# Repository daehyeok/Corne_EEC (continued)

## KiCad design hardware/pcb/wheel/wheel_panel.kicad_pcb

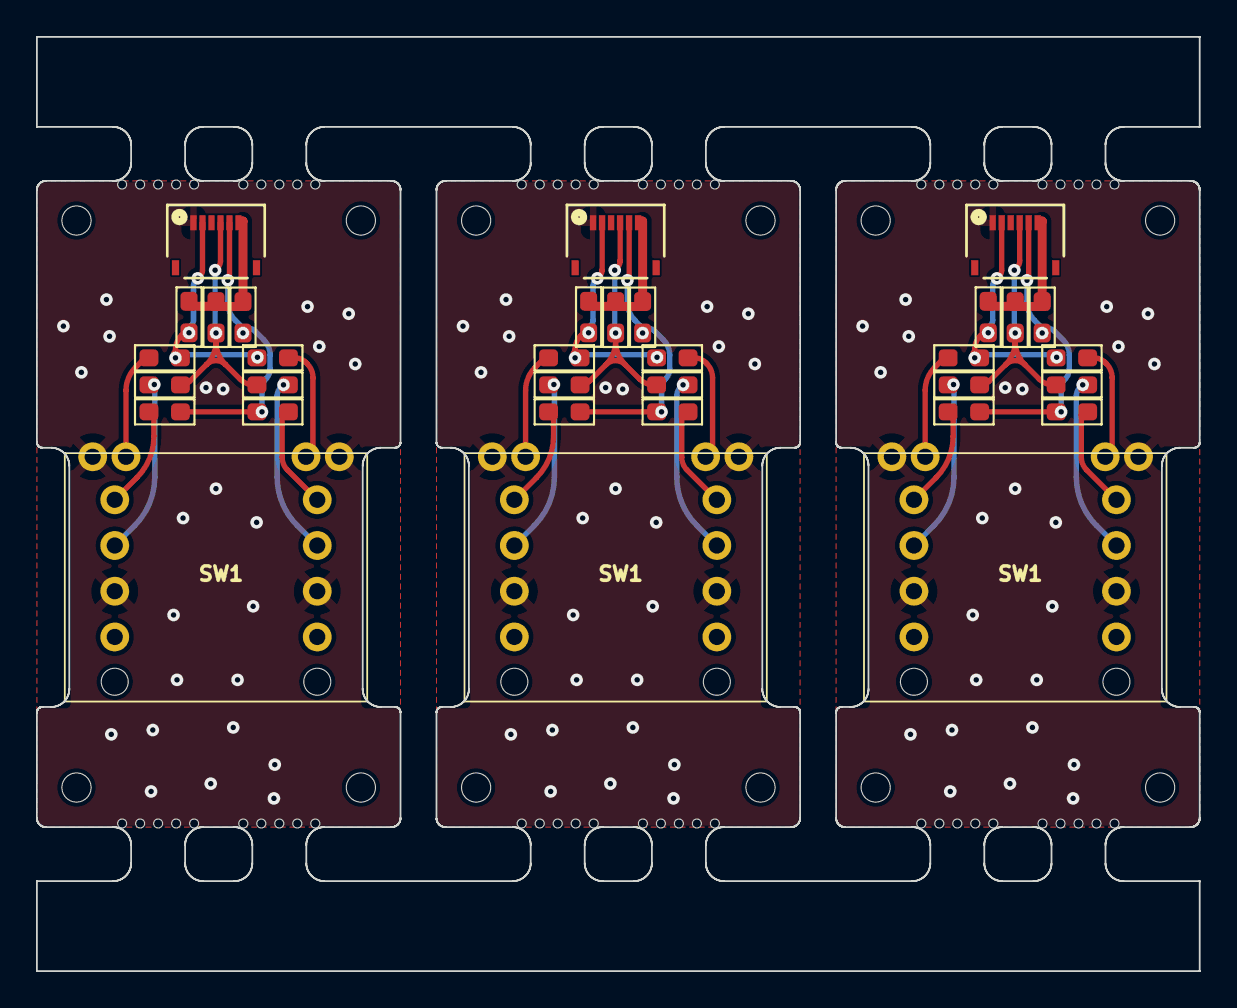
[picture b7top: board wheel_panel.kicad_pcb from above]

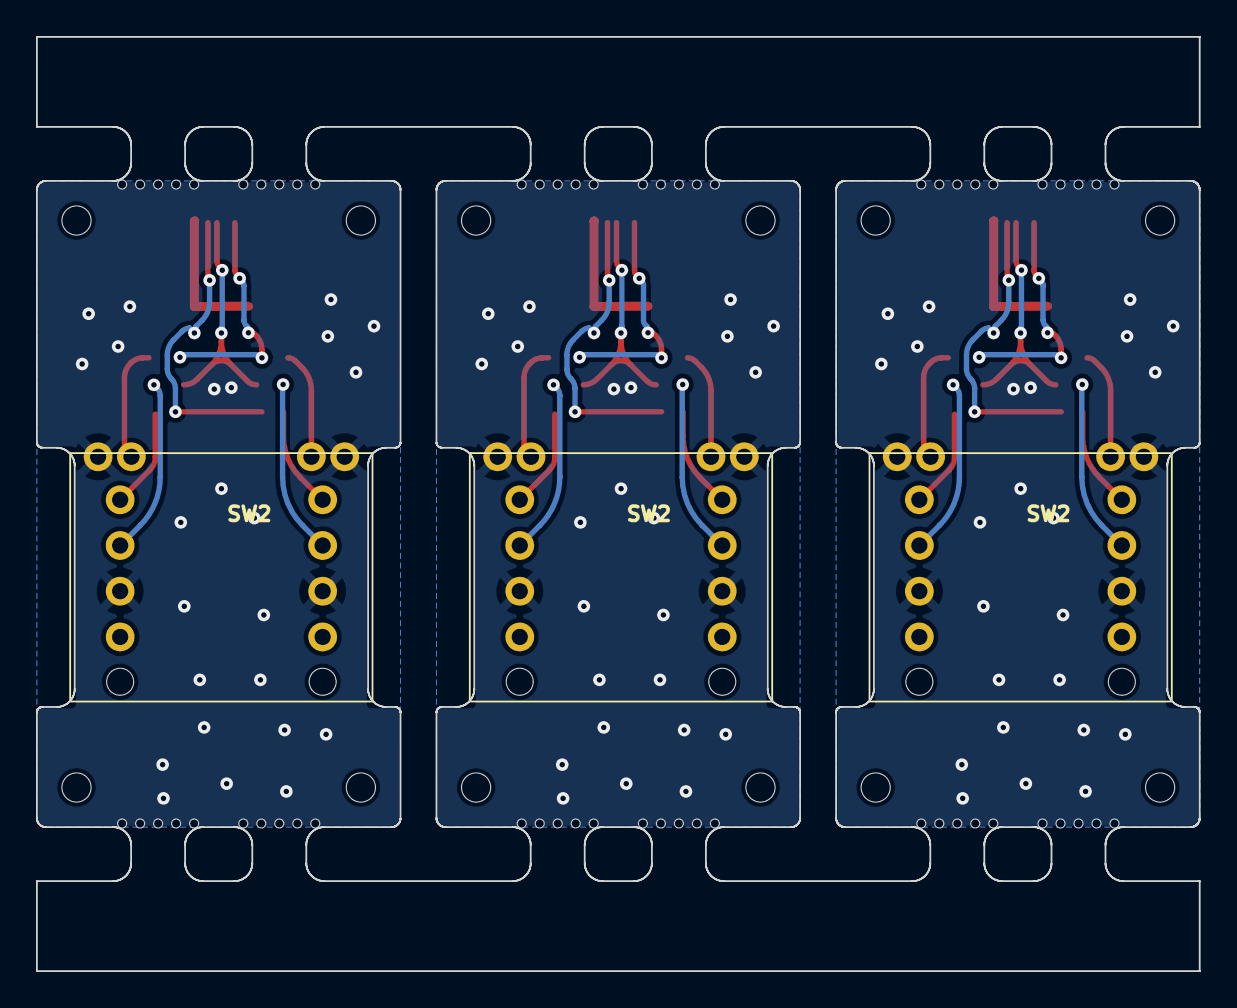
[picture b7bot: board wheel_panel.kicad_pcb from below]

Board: 2 copper layers, 64.6 x 51.9 mm, 108 parts (3 on the bottom side), 33 nets.

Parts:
H3, H3#2, H3#3, H4, H4#2, H4#3, H5, H5#2, H5#3, H6, H6#2, H6#3: SMT-SO-M1.6-with-ring
J4, J4#2, J4#3: HRS_FH34SRJ-06S-0.5SH(50); CONN6x1_FH34SRJ-6S-0.5SH50_HIR
KiKit_MB_1_1, KiKit_MB_1_2, KiKit_MB_1_3, KiKit_MB_1_4, KiKit_MB_1_5, KiKit_MB_2_1, KiKit_MB_2_2, KiKit_MB_2_3, KiKit_MB_2_4, KiKit_MB_2_5, KiKit_MB_3_1, KiKit_MB_3_2, KiKit_MB_3_3, KiKit_MB_3_4, KiKit_MB_3_5, KiKit_MB_4_1, KiKit_MB_4_2, KiKit_MB_4_3, KiKit_MB_4_4, KiKit_MB_4_5, KiKit_MB_5_1, KiKit_MB_5_2, KiKit_MB_5_3, KiKit_MB_5_4, KiKit_MB_5_5, KiKit_MB_6_1, KiKit_MB_6_2, KiKit_MB_6_3, KiKit_MB_6_4, KiKit_MB_6_5, KiKit_MB_7_1, KiKit_MB_7_2, KiKit_MB_7_3, KiKit_MB_7_4, KiKit_MB_7_5, KiKit_MB_8_1, KiKit_MB_8_2, KiKit_MB_8_3, KiKit_MB_8_4, KiKit_MB_8_5, KiKit_MB_9_1, KiKit_MB_9_2, KiKit_MB_9_3, KiKit_MB_9_4, KiKit_MB_9_5, KiKit_MB_10_1, KiKit_MB_10_2, KiKit_MB_10_3, KiKit_MB_10_4, KiKit_MB_10_5, KiKit_MB_11_1, KiKit_MB_11_2, KiKit_MB_11_3, KiKit_MB_11_4, KiKit_MB_11_5, KiKit_MB_12_1, KiKit_MB_12_2, KiKit_MB_12_3, KiKit_MB_12_4, KiKit_MB_12_5: NPTH
R1, R1#2, R1#3, R2, R2#2, R2#3, R3, R3#2, R3#3: 10k; R_0603_1608Metric_Pad1.05x0.95mm_HandSolder
R4, R4#2, R4#3, R5, R5#2, R5#3, R6, R6#2, R6#3, R7, R7#2, R7#3, R8, R8#2, R8#3, R9, R9#2, R9#3: 0; R_0603_1608Metric_Pad1.05x0.95mm_HandSolder
SW1, SW1#2, SW1#3, SW2, SW2#2, SW2#3: RotaryEncoder_Switch; EVQWGD001

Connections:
Board_0-+3.3V: J4#3.6, R1#2.1, R2#3.1, R3.2
Board_0-ACCS_1: J4#3.5, R1#2.2, R4#2.1, R7#3.1
Board_0-ACCS_2: J4#3.4, R2#3.2, R5#2.1, R8#3.1
Board_0-ACCS_4: J4#3.2, R3.1, R6#3.2, R9#3.2
Board_0-GND: J4#3.1, SW1#3.C, SW1#3.S1, SW2#3.C, SW2#3.S1
Board_0-Net-(R4-Pad2): R4#2.2, SW1#3.A
Board_0-Net-(R5-Pad2): R5#2.2, SW1#3.B
Board_0-Net-(R6-Pad1): R6#3.1, SW1#3.S2
Board_0-Net-(R7-Pad2): R7#3.2, SW2#3.A
Board_0-Net-(R8-Pad2): R8#3.2, SW2#3.B
Board_0-Net-(R9-Pad1): R9#3.1, SW2#3.S2
Board_1-+3.3V: J4.6, R1#3.1, R2.1, R3#3.2
Board_1-ACCS_1: J4.5, R1#3.2, R4#3.1, R7#2.1
Board_1-ACCS_2: J4.4, R2.2, R5#3.1, R8#2.1
Board_1-ACCS_4: J4.2, R3#3.1, R6.2, R9.2
Board_1-GND: J4.1, SW1#2.C, SW1#2.S1, SW2#2.C, SW2#2.S1
Board_1-Net-(R4-Pad2): R4#3.2, SW1#2.A
Board_1-Net-(R5-Pad2): R5#3.2, SW1#2.B
Board_1-Net-(R6-Pad1): R6.1, SW1#2.S2
Board_1-Net-(R7-Pad2): R7#2.2, SW2#2.A
Board_1-Net-(R8-Pad2): R8#2.2, SW2#2.B
Board_1-Net-(R9-Pad1): R9.1, SW2#2.S2
Board_2-+3.3V: J4#2.6, R1.1, R2#2.1, R3#2.2
Board_2-ACCS_1: J4#2.5, R1.2, R4.1, R7.1
Board_2-ACCS_2: J4#2.4, R2#2.2, R5.1, R8.1
Board_2-ACCS_4: J4#2.2, R3#2.1, R6#2.2, R9#2.2
Board_2-GND: J4#2.1, SW1.C, SW1.S1, SW2.C, SW2.S1
Board_2-Net-(R4-Pad2): R4.2, SW1.A
Board_2-Net-(R5-Pad2): R5.2, SW1.B
Board_2-Net-(R6-Pad1): R6#2.1, SW1.S2
Board_2-Net-(R7-Pad2): R7.2, SW2.A
Board_2-Net-(R8-Pad2): R8.2, SW2.B
Board_2-Net-(R9-Pad1): R9#2.1, SW2.S2

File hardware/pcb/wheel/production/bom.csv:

Designator,Footprint,Quantity,Value,LCSC Part #
"H3_3, H3_2, H3, H4_3, H4_2, H4, H5_3, H5_2, H5, H6_3, H6_2, H6",SMT-SO-M1.6-with-ring,12,~,
"J4_3, J4_2, J4",CONN6x1_FH34SRJ-6S-0.5SH50_HIR,3,HRS_FH34SRJ-06S-0.5SH(50),
"R1_3, R1_2, R1, R2_3, R2_2, R2, R3_3, R3_2, R3",0603,9,10k,
"R4_3, R4_2, R4, R5_3, R5_2, R5, R6_3, R6_2, R6, R7_3, R7_2, R7, R8_3, R8_2, R8, R9_3, R9_2, R9",0603,18,0,
"SW1_3, SW1_2, SW1, SW2_3, SW2_2, SW2",EVQWGD001,6,RotaryEncoder_Switch,

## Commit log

2022-01-23 Upload
2022-01-30 Upload of firmwares
    BEWARE:
    - `crkbd_ecwl_default.hex` is compiled with gonnoc's own fork and branch, based on the old QMK 6.1
    - `crkbd_ecrevival_default.hex` is compiled with the current stable QMK, it has some flaws, described below, but the general functionality is preserved.
    As of now the Original ECWL has a wider range of sensibility. The EC revival one doesn't have that fine control. I'm working on a patch/rework of the custom matrix implementation to solve this.
    For proper testing and fine tuning I STRONGLY advice to self compile the branch that gonnoc has (qmk_firmware, dev/ecwl).
2022-01-30 Codebase upload
    Still in WIP on my main QMK fork. Gonnoc's OG code is available through the dev/ecwl branch of his own fork.
2022-01-30 Update of current release
2022-01-31 Add of standard mounting compatible PCBs
2022-01-31 Update of rev commit to include extra screw mount
2022-02-03 Updated Firmware
2022-02-03 PCB Update and STEP upload
2022-02-03 Update to fix Pimoroni skipping issue
2022-02-04 Upload STEP files
2022-02-08 Firmware updated
    Default firmware now is separate from the trackball one.
2022-02-22 Create cipulot_kicad_parts
2022-02-22 Update fp-info-cache
2022-02-22 Update cipulot_kicad_parts
2022-02-22 Updated EC pad footprint
2022-02-28 Fix footprint
    Fix of outdated footprint that introduced a "no track" rule where it was not supposed to be implemented.
2022-03-08 Folder structure update
2022-03-16 Update matrix.c
    Fix for compialtion error trown by the compiler dated 3/15/2022. Error at compilation was given saying that the prev function name was predefined in other subfunctions called by the firmware. This mi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
2022-03-16 Update config.h
    Previously defined values changed after seeing that the deviation in the values from the left side was caused by the specific pro micro board I was using.
2022-03-22 Addition of ECWL compatible Topre plate
2022-03-22 Update production file format
2022-04-18 Moved 3d models from PCB to Assets
2022-04-18 Update of PCB and models
2022-04-19 Update files for JLC production (minimal assembly)
2022-04-19 Reupload gerber
2022-04-27 Consolidation folder in prep for Rev2
2022-04-27 Moved 3d models to dedicated RevX folder
2022-05-12 Fix pad numbering
2022-08-09 FIX Production files
    Fix to the production files that caused one of the 2 EC pads to be merged with the ground plane.
2023-06-23 remove unsued files
2023-06-23 init
2023-06-23 Remove funding doc
2023-07-18 Init STM32G0 PCB
2023-07-18 Fix capacitor, resistor values
2023-07-20 Add plate and assembly stand laser cut
2023-07-23 Add 3d files and rendering image
2023-07-23 Reorganize
2023-07-24 roate FFC Connector
2023-07-24 updated rendering image
2023-08-06 temp
2023-08-07 Left init
2023-08-12 Right init
2023-08-13 usb hib init
2023-08-14 preproduction
2025-08-21 rev2
2025-08-22 rev2 pre production
2025-08-25 init memory
2025-08-29 add pull up register for I2C.
2025-08-31 fix acc connection.
2025-08-31 update schema.
2025-09-03 wheel
2025-09-05 production
2025-09-08 Change crystal
2025-09-08 back
2025-09-16 init 3d case.
2025-09-18 Generate production files.
2025-09-27 stencil temp
2025-09-28 Rev 2.1
2025-10-11 shield outline.
